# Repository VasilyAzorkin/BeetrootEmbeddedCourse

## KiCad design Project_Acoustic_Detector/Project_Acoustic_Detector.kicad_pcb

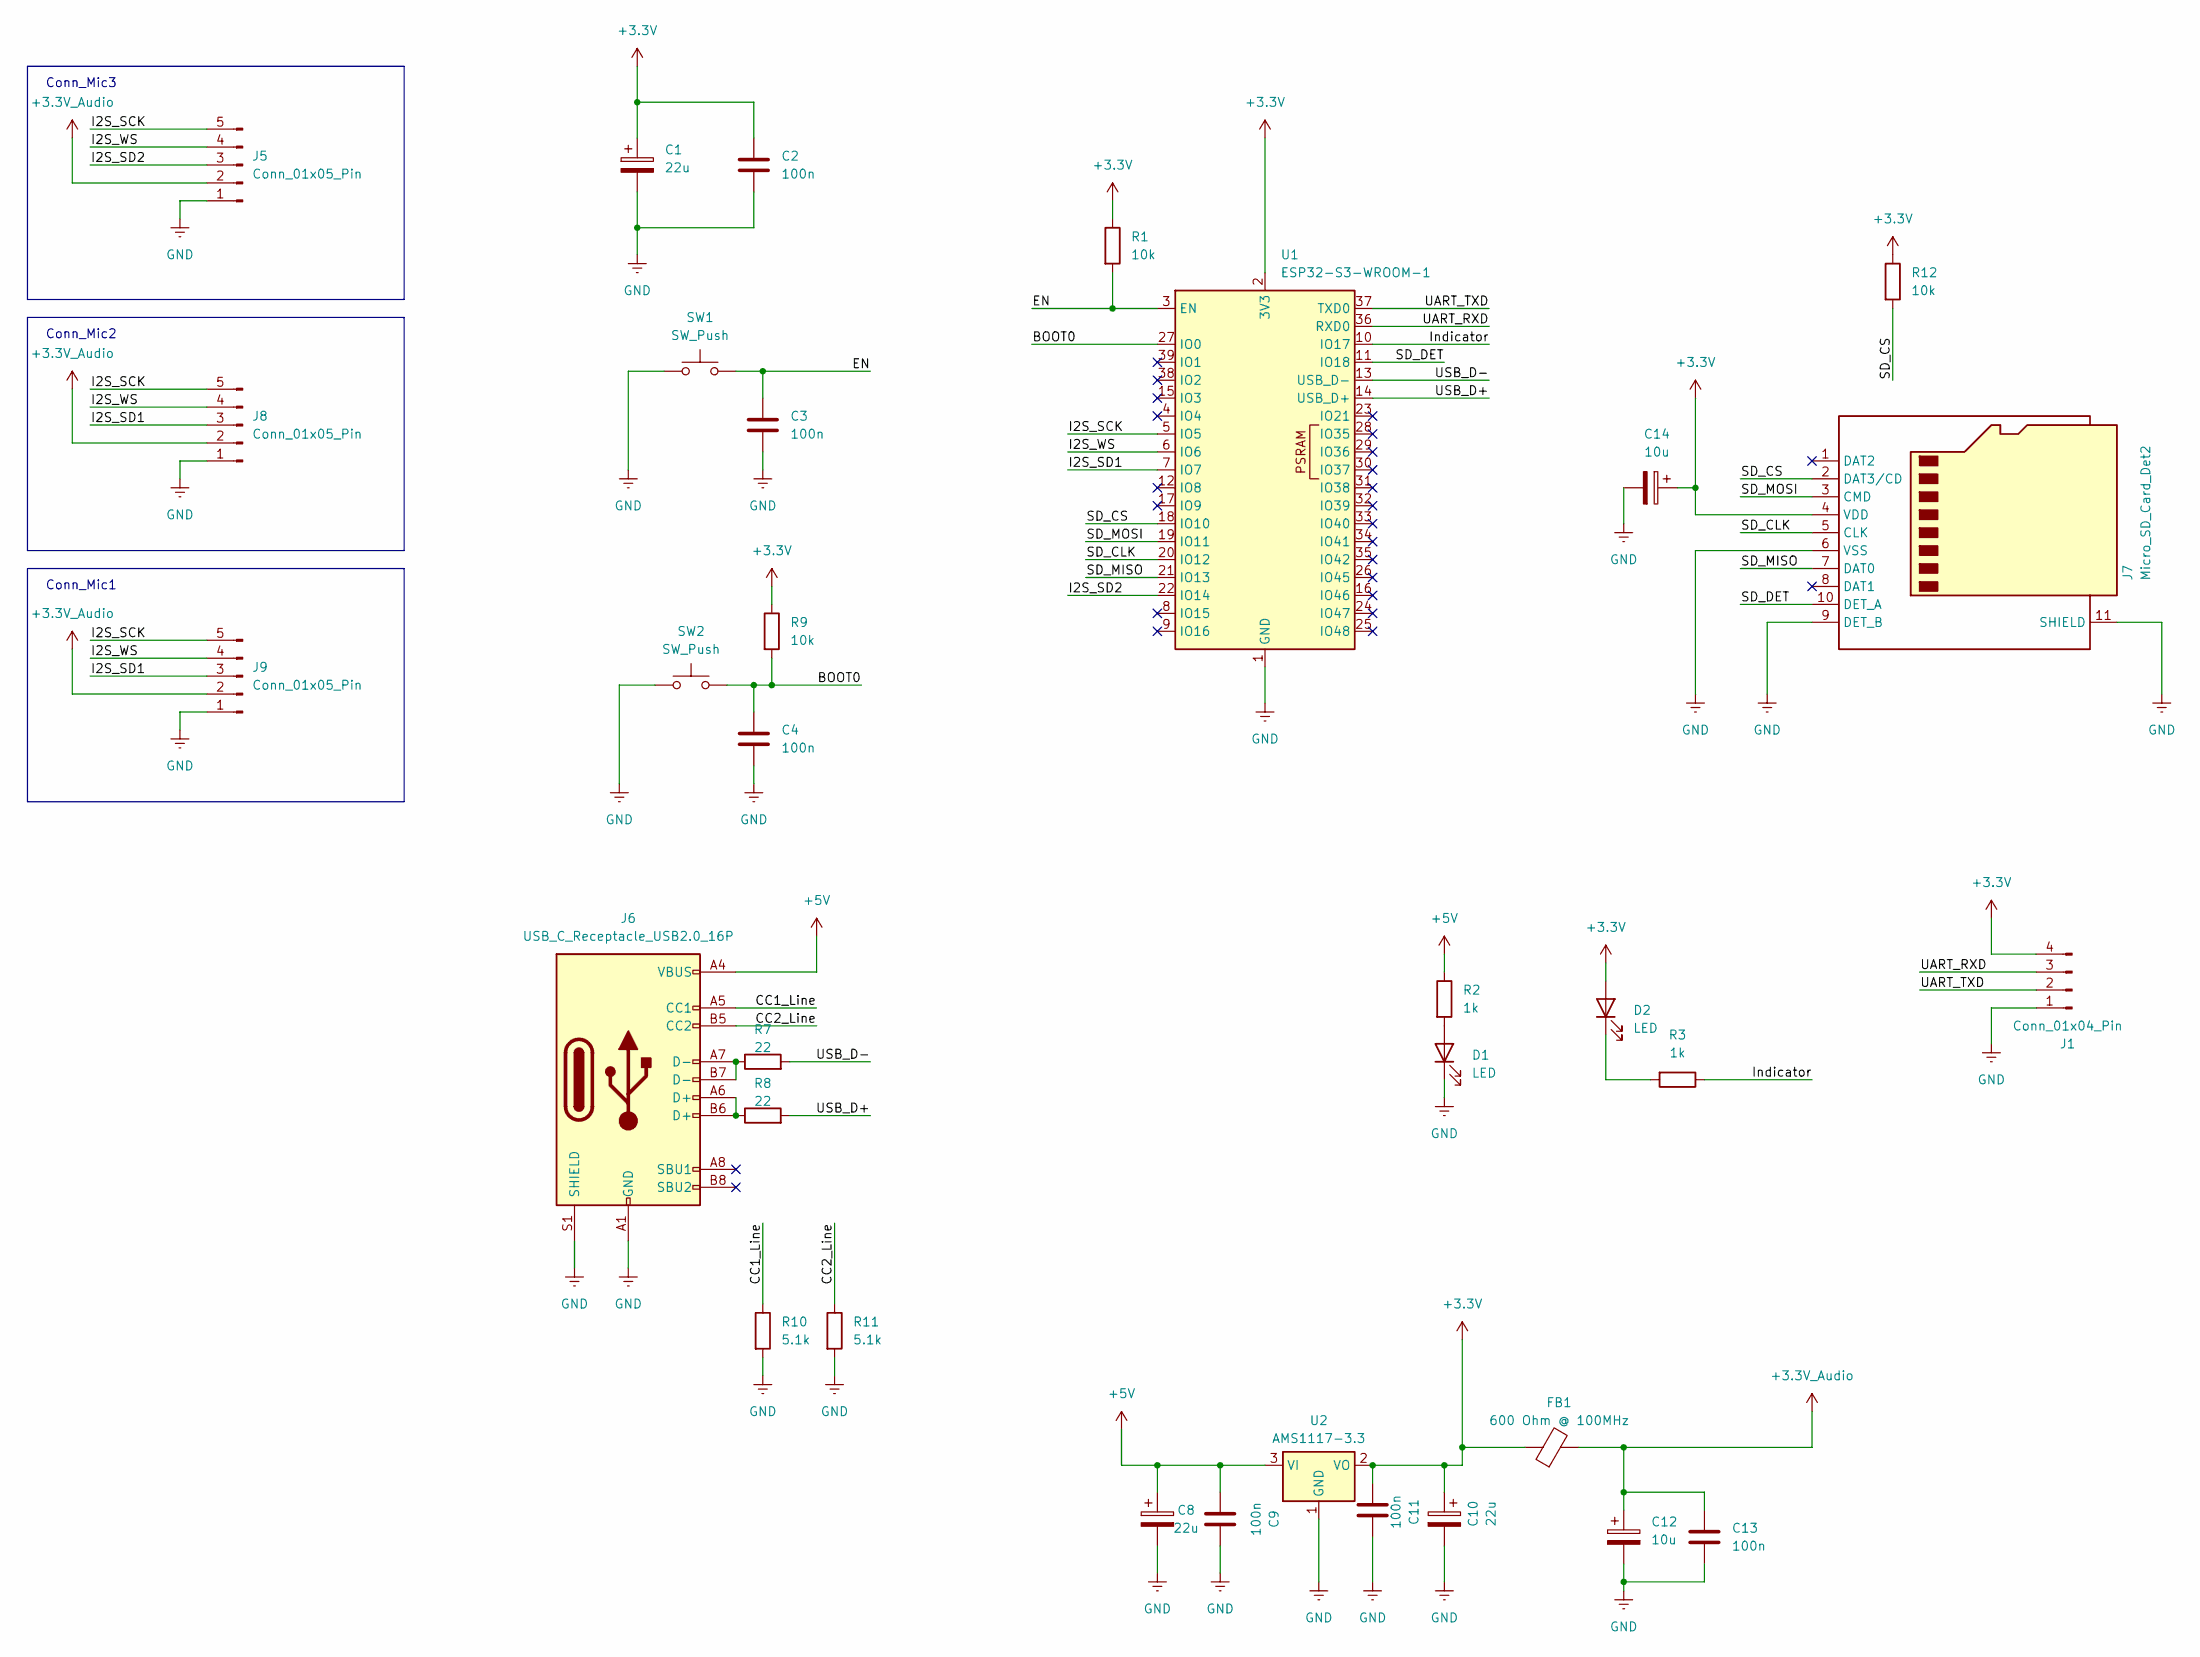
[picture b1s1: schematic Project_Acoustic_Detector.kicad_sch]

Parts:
C1, C8, C10: 22u; CP_EIA-3216-18_Kemet-A_HandSolder
C2, C3, C4, C9, C11, C13: 100n; C_1206_3216Metric_Pad1.33x1.80mm_HandSolder
C12, C14: 10u; CP_EIA-3216-18_Kemet-A_HandSolder
D1, D2: LED; LED_1206_3216Metric_Pad1.42x1.75mm_HandSolder
FB1: 600 Ohm @ 100MHz; L_1206_3216Metric_Pad1.22x1.90mm_HandSolder
J1: Conn_01x04_Pin; PinHeader_1x04_P2.54mm_Vertical
J5, J8, J9: Conn_01x05_Pin; PinHeader_1x05_P2.54mm_Vertical
J6: USB_C_Receptacle_USB2.0_16P; USB_C_Receptacle_GCT_USB4085
J7: Micro_SD_Card_Det2; microSD_HC_Hirose_DM3D-SF
R1, R9, R12: 10k; R_1206_3216Metric_Pad1.30x1.75mm_HandSolder
R2, R3: 1k; R_1206_3216Metric_Pad1.30x1.75mm_HandSolder
R7, R8: 22; R_1206_3216Metric_Pad1.30x1.75mm_HandSolder
R10, R11: 5.1k; R_1206_3216Metric_Pad1.30x1.75mm_HandSolder
SW1, SW2: SW_Push; SW_SPST_PTS645Sx43SMTR92
U1: ESP32-S3-WROOM-1
U2: AMS1117-3.3; SOT-223-3_TabPin2

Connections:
+3.3V: C1.1, C2.1, C10.1, C11.1, C14.1, D2.2 (A), FB1.1, J1.4, J7.4 (VDD), R1.1, R9.1, R12.1, U1.2 (3V3), U2.2 (VO)
+3.3V_Audio: C12.1, C13.2, FB1.2, J5.2, J8.2, J9.2
+5V: C8.1, C9.1, J6.A4 (VBUS), J6.A9 (VBUS), J6.B4 (VBUS), J6.B9 (VBUS), R2.1, U2.3 (VI)
/BOOT0: C4.1, R9.2, SW2.2, U1.27 (IO0)
/CC1_Line: J6.A5 (CC1), R10.1
/CC2_Line: J6.B5 (CC2), R11.1
/EN: C3.1, R1.2, SW1.2, U1.3 (EN)
/I2S_SCK: J5.5, J8.5, J9.5, U1.5 (IO5)
/I2S_SD1: J8.3, J9.3, U1.7 (IO7)
/I2S_SD2: J5.3, U1.22 (IO14)
/I2S_WS: J5.4, J8.4, J9.4, U1.6 (IO6)
/Indicator: R3.1, U1.10 (IO17)
/SD_CLK: J7.5 (CLK), U1.20 (IO12)
/SD_CS: J7.2 (DAT3/CD), R12.2, U1.18 (IO10)
/SD_DET: J7.10 (DET_A), U1.11 (IO18)
/SD_MISO: J7.7 (DAT0), U1.21 (IO13)
/SD_MOSI: J7.3 (CMD), U1.19 (IO11)
/UART_RXD: J1.3, U1.36 (RXD0)
/UART_TXD: J1.2, U1.37 (TXD0)
/USB_D+: R8.2, U1.14 (USB_D+)
/USB_D-: R7.2, U1.13 (USB_D-)
GND: C1.2, C2.2, C3.2, C4.2, C8.2, C9.2, C10.2, C11.2, C12.2, C13.1, C14.2, D1.1 (K), J1.1, J5.1, J6.A1 (GND), J6.A12 (GND), J6.B1 (GND), J6.B12 (GND), J6.S1 (SHIELD), J7.6 (VSS), J7.9 (DET_B), J7.11 (SHIELD), J8.1, J9.1, R10.2, R11.2, SW1.1, SW2.1, U1.1 (GND), U1.40 (GND), U1.41 (GND), U2.1 (GND)
unnamed: D1.2 (A), R2.2
unnamed: D2.1 (K), R3.2
unnamed: J6.A6 (D+), J6.B6 (D+), R8.1
unnamed: J6.A7 (D-), J6.B7 (D-), R7.1

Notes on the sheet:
Conn_Mic2
Conn_Mic1
Conn_Mic3

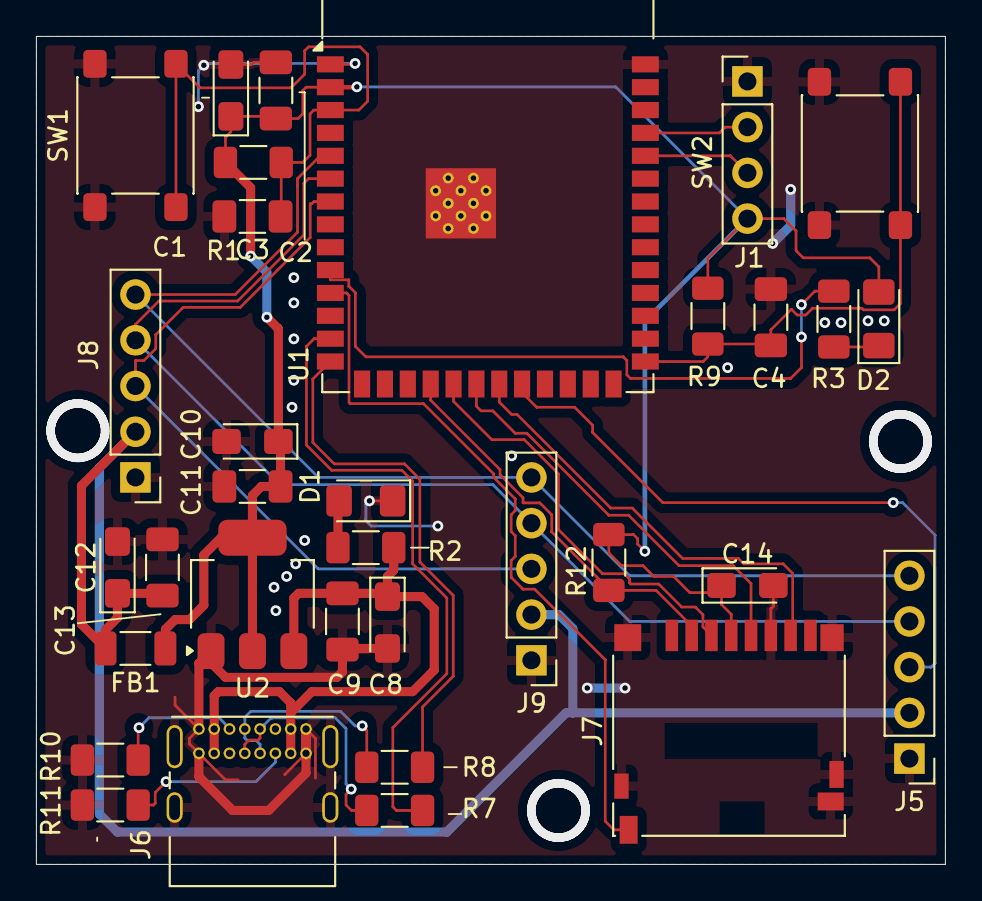
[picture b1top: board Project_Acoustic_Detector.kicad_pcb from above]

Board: 2 copper layers, 50.5 x 46.0 mm, 33 parts (0 on the bottom side), 26 nets.

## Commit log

2026-01-25 Final fix: structure and ignore
2026-01-27 Added Stopwatch class, implemented whole logic
2026-01-28 Added screenshot of the serial port output
2026-02-03 Added encoder calculator
2026-02-03 Removed unused state
2026-02-05 Added backspaces
2026-02-08 added ADC(Potentiometer) + SERVO driver code
2026-02-08 added gif animation with terminal logs
2026-02-20 added ESP32 project
2026-02-20 added STM32 project
2026-02-26 added new projects
2026-03-01 Finished Relay measuring code
2026-03-01 Added HW 21 superloop proj
2026-03-11 Added 4 exercises for Button Interrupts Homework
2026-03-21 Added code using legacy timer
2026-03-21 Added timers handler project with gptimer driver usage
2026-03-22 Homework 26. Debounce in ESP-IDF
2026-03-22 Added exercise 4
2026-03-24 Added miniproject module 2
2026-03-24 Added HW 28 - STM32: button and led
2026-03-25 Added HW 29 - STM32 via VS Code: toggle led
2026-03-29 Add HW 31 (ADC and potentiometer) code
2026-04-04 added code for HW 32
2026-04-14 added KiCad project
2026-04-14 updated KiCad project
2026-04-19 added homework 33 pwm for motor and led
2026-04-22 init commit. added data structure for sample recording
2026-04-22 Started adding HW for buzzer using PWM
2026-04-26 Updated probe and Detector
2026-04-28 Added init of mics
2026-04-28 Added math of mics
2026-04-29 Added calculations for angle and FFR for frequency peaks
